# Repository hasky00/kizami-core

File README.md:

# kizami-core

The FPGA side of [Kizami](https://github.com/hasky00/kizami) — a Nostr-timestamped
audio witness. Runs on the open-hardware Alhambra II (iCE40HX4K).

- `rtl/` — Verilog. `timecode.v` is the HH:MM:SS:FF counter, `top.v` maps it to LEDs.
- `icestudio/` — `.ice` designs for Icestudio / FPGALab.
- `labs/` — FPGALab workbench configs.
- `docs/` — LTC frame layout and the roadmap.

## Simulate (no hardware)
1. Open `icestudio/` design in Icestudio, build once so `ice-build/` exists.
2. `fpga-lab --ice icestudio/<design>.ice --clock-hz 1200000` (slow mode, readable LEDs).

## Build & flash (Alhambra II)
```
pip install apio && apio install --all
apio build && apio upload
```

LED0–4 = frame count in binary, LED7 = blinks once per second.

License: MIT

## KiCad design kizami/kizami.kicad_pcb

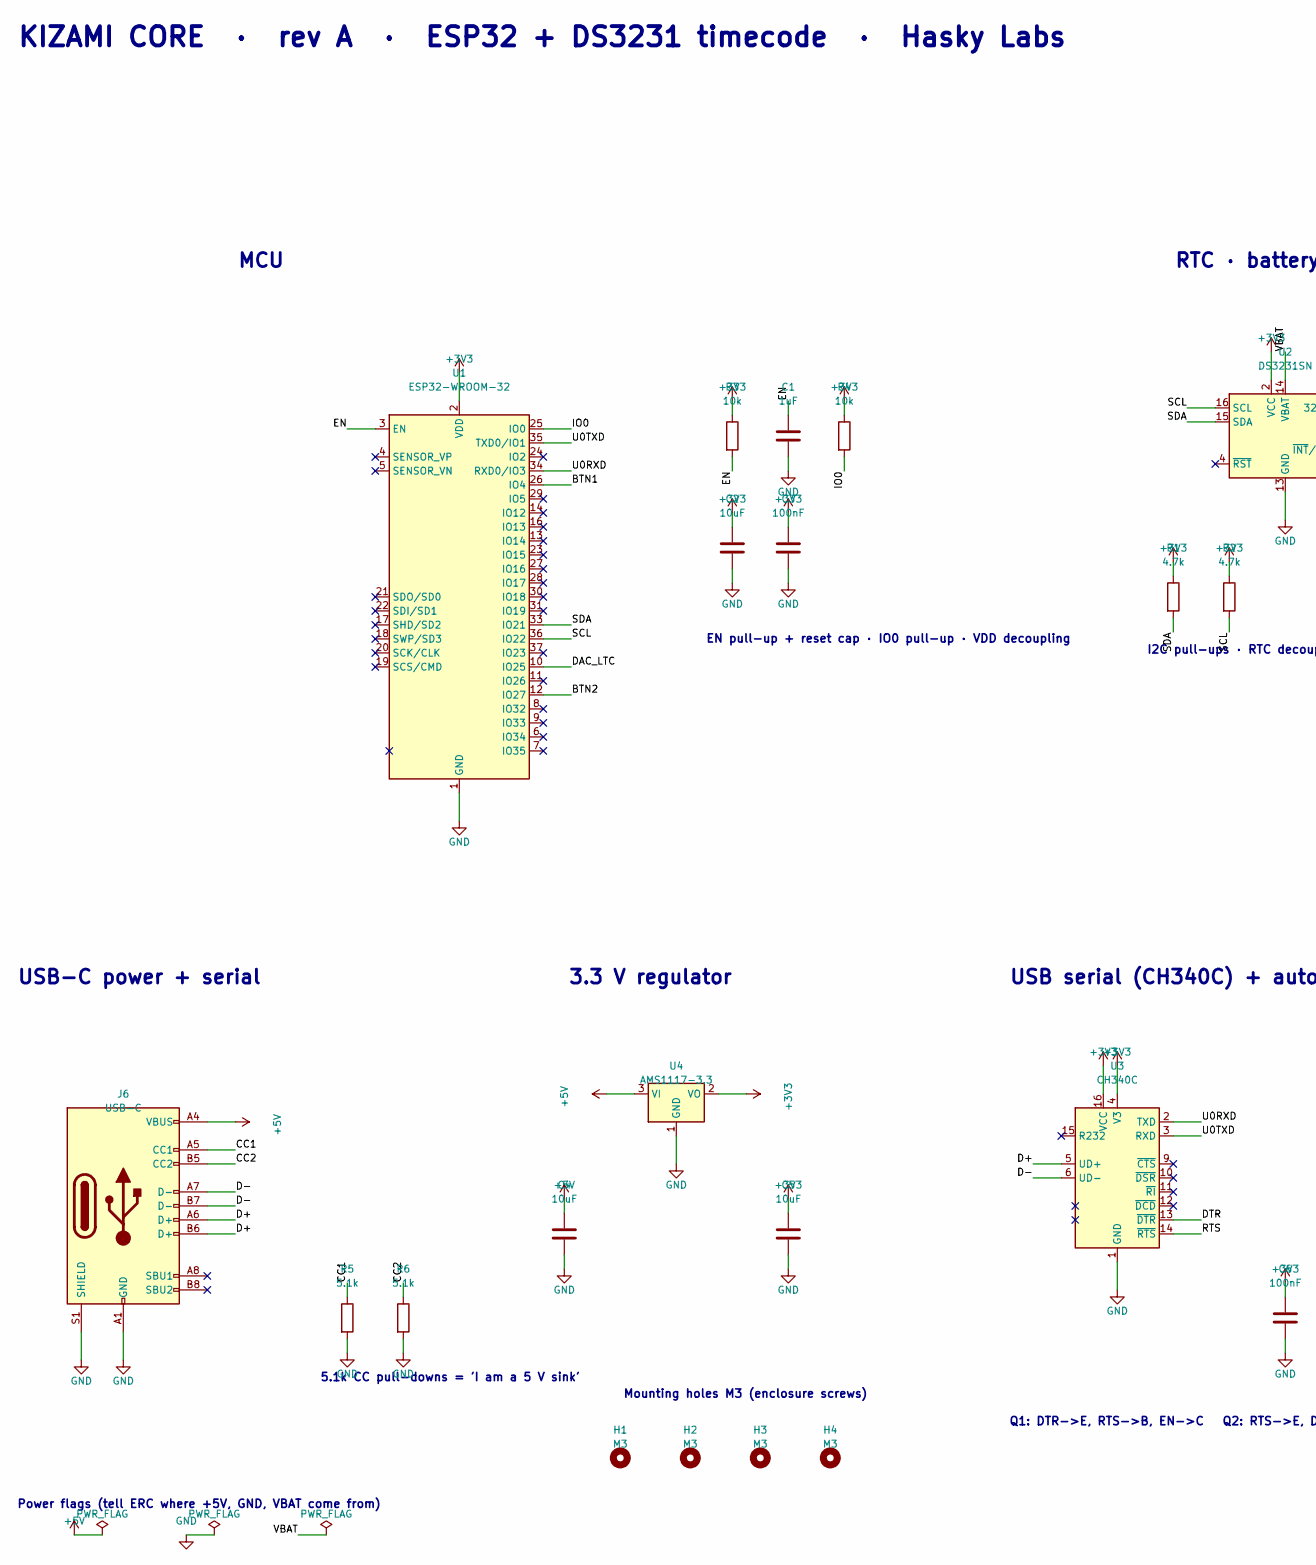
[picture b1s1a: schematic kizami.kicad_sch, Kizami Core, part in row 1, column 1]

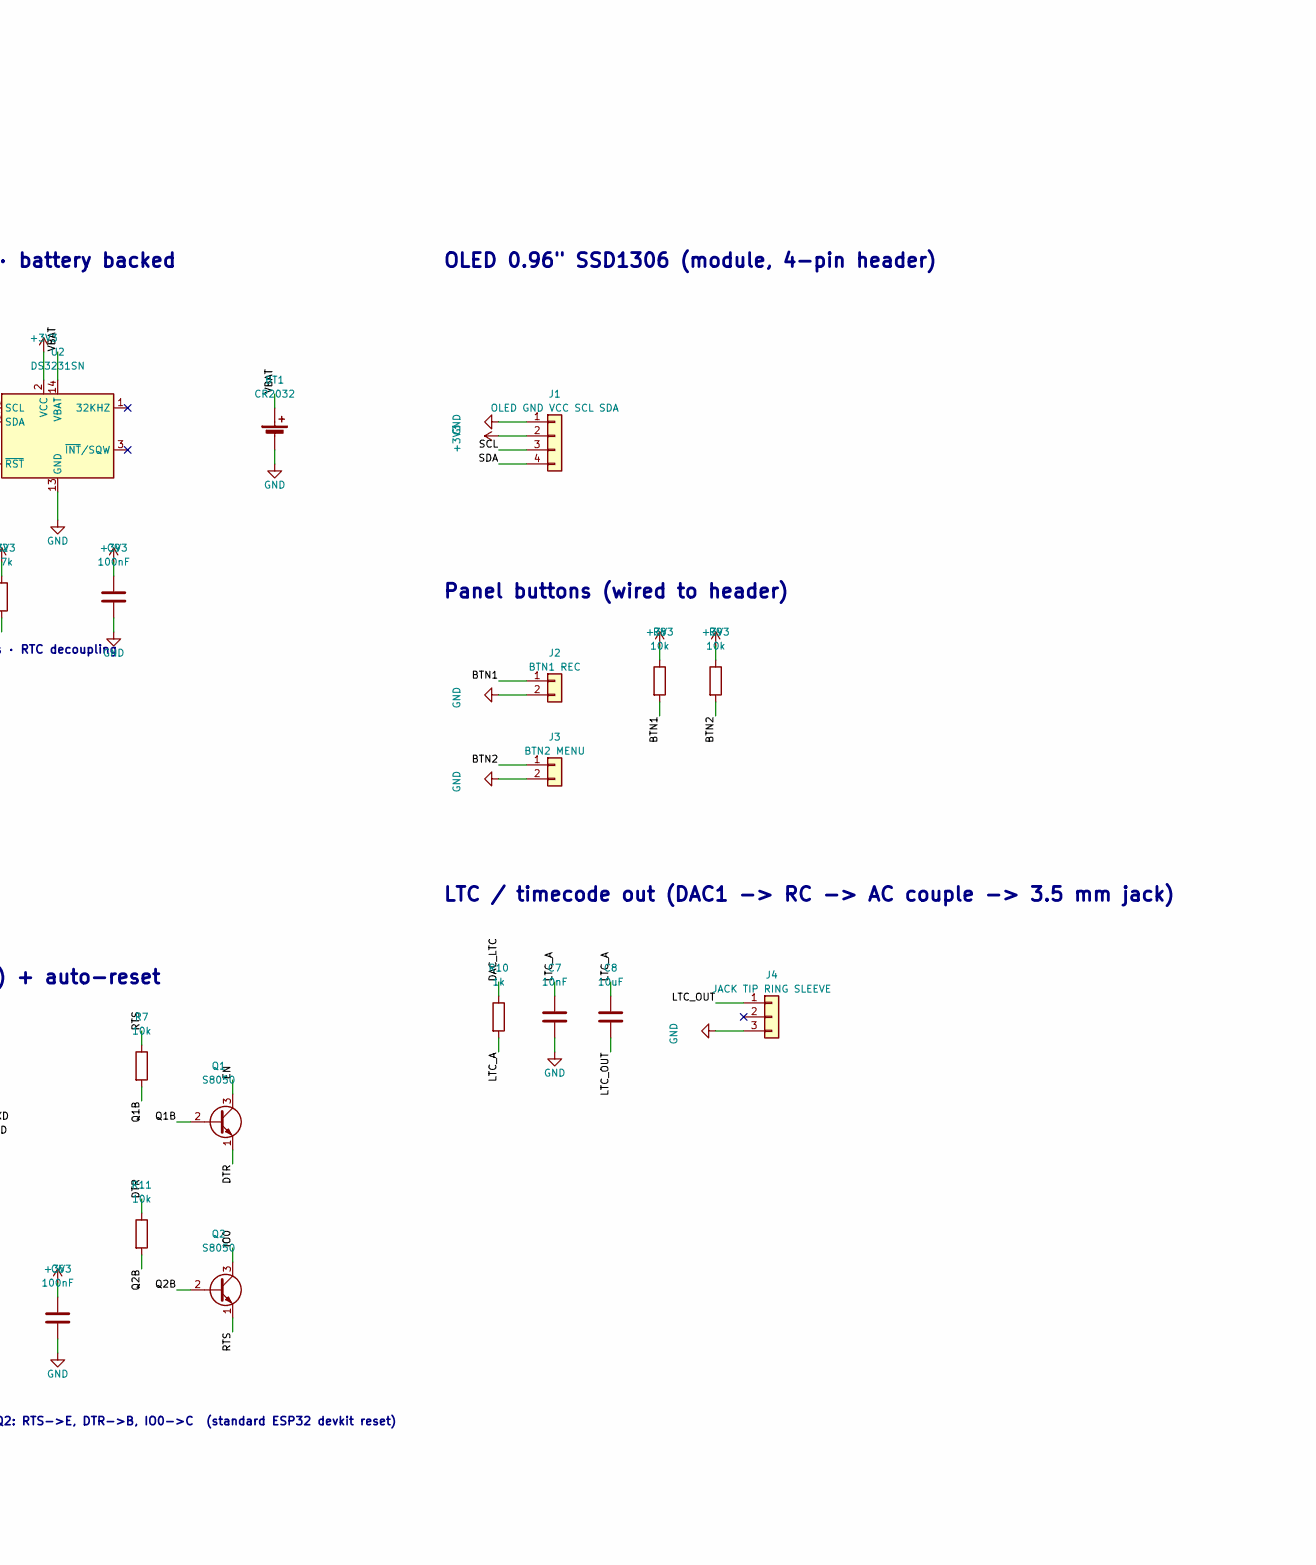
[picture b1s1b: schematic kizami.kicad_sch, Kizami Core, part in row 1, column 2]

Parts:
BT1: CR2032; BatteryHolder_Keystone_3034_1x20mm
C1: 1uF; C_0603_1608Metric; LCSC C15849
C2, C4, C5, C8: 10uF; C_0603_1608Metric; LCSC C19702
C3, C6, C9: 100nF; C_0603_1608Metric; LCSC C14663
C7: 10nF; C_0603_1608Metric; LCSC C57112
H1, H2, H3, H4: M3; MountingHole_3.2mm_M3
J1: OLED GND VCC SCL SDA; PinHeader_1x04_P2.54mm_Vertical
J2: BTN1 REC; PinHeader_1x02_P2.54mm_Vertical
J3: BTN2 MENU; PinHeader_1x02_P2.54mm_Vertical
J4: JACK TIP RING SLEEVE; PinHeader_1x03_P2.54mm_Vertical
J6: USB-C; USB_C_Receptacle_HRO_TYPE-C-31-M-12; LCSC C165948
Q1, Q2: S8050; SOT-23; LCSC C2146
R1, R2: 4.7k; R_0603_1608Metric; LCSC C23162
R3, R4, R7, R8, R9, R11: 10k; R_0603_1608Metric; LCSC C25804
R5, R6: 5.1k; R_0603_1608Metric; LCSC C23186
R10: 1k; R_0603_1608Metric; LCSC C21190
U1: ESP32-WROOM-32; LCSC C82899
U2: DS3231SN; SOIC-16W_7.5x10.3mm_P1.27mm
U3: CH340C; SOIC-16_3.9x9.9mm_P1.27mm; LCSC C84681
U4: AMS1117-3.3; SOT-223-3_TabPin2; LCSC C6186

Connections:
+3V3: C2.1, C3.1, C5.1, C6.1, C9.1, J1.2, R1.1, R2.1, R3.1, R4.1, R8.1, R9.1, U1.2 (VDD), U2.2 (VCC), U3.4 (V3), U3.16 (VCC), U4.2 (VO)
+5V: C4.1, J6.A4 (VBUS), J6.A9 (VBUS), J6.B4 (VBUS), J6.B9 (VBUS), U4.3 (VI)
/BTN1: J2.1, R8.2, U1.26 (IO4)
/BTN2: J3.1, R9.2, U1.12 (IO27)
/CC1: J6.A5 (CC1), R5.1
/CC2: J6.B5 (CC2), R6.1
/D+: J6.A6 (D+), J6.B6 (D+), U3.5 (UD+)
/D-: J6.A7 (D-), J6.B7 (D-), U3.6 (UD-)
/DAC_LTC: R10.1, U1.10 (IO25)
/DTR: Q1.1 (E), R11.1, U3.13 (~DTR)
/EN: C1.1, Q1.3 (C), R3.2, U1.3 (EN)
/IO0: Q2.3 (C), R4.2, U1.25 (IO0)
/LTC_A: C7.1, C8.1, R10.2
/LTC_OUT: C8.2, J4.1
/Q1B: Q1.2 (B), R7.2
/Q2B: Q2.2 (B), R11.2
/RTS: Q2.1 (E), R7.1, U3.14 (~RTS)
/SCL: J1.3, R2.2, U1.36 (IO22), U2.16 (SCL)
/SDA: J1.4, R1.2, U1.33 (IO21), U2.15 (SDA)
/U0RXD: U1.34 (RXD0/IO3), U3.2 (TXD)
/U0TXD: U1.35 (TXD0/IO1), U3.3 (RXD)
/VBAT: BT1.1 (+), U2.14 (VBAT)
GND: BT1.2 (-), C1.2, C2.2, C3.2, C4.2, C5.2, C6.2, C7.2, C9.2, J1.1, J2.2, J3.2, J4.3, J6.A1 (GND), J6.A12 (GND), J6.B1 (GND), J6.B12 (GND), J6.S1 (SHIELD), R5.2, R6.2, U1.1 (GND), U1.15 (GND), U1.38 (GND), U1.39 (GND), U2.5 (GND), U2.6 (GND), U2.7 (GND), U2.8 (GND), U2.9 (GND), U2.10 (GND), U2.11 (GND), U2.12 (GND), U2.13 (GND), U3.1 (GND), U4.1 (GND)

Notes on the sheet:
KIZAMI CORE · rev A · ESP32 + DS3231 timecode · Hasky Labs
MCU
EN pull-up + reset cap · IO0 pull-up · VDD decoupling
RTC · battery backed
I2C pull-ups · RTC decoupling
OLED 0.96" SSD1306 (module, 4-pin header)
Panel buttons (wired to header)
LTC / timecode out (DAC1 -> RC -> AC couple -> 3.5 mm jack)
USB-C power + serial
5.1k CC pull-downs = 'I am a 5 V sink'
3.3 V regulator
USB serial (CH340C) + auto-reset
Q1: DTR->E, RTS->B, EN->C Q2: RTS->E, DTR->B, IO0->C (standard ESP32 devkit reset)
Power flags (tell ERC where +5V, GND, VBAT come from)
Mounting holes M3 (enclosure screws)

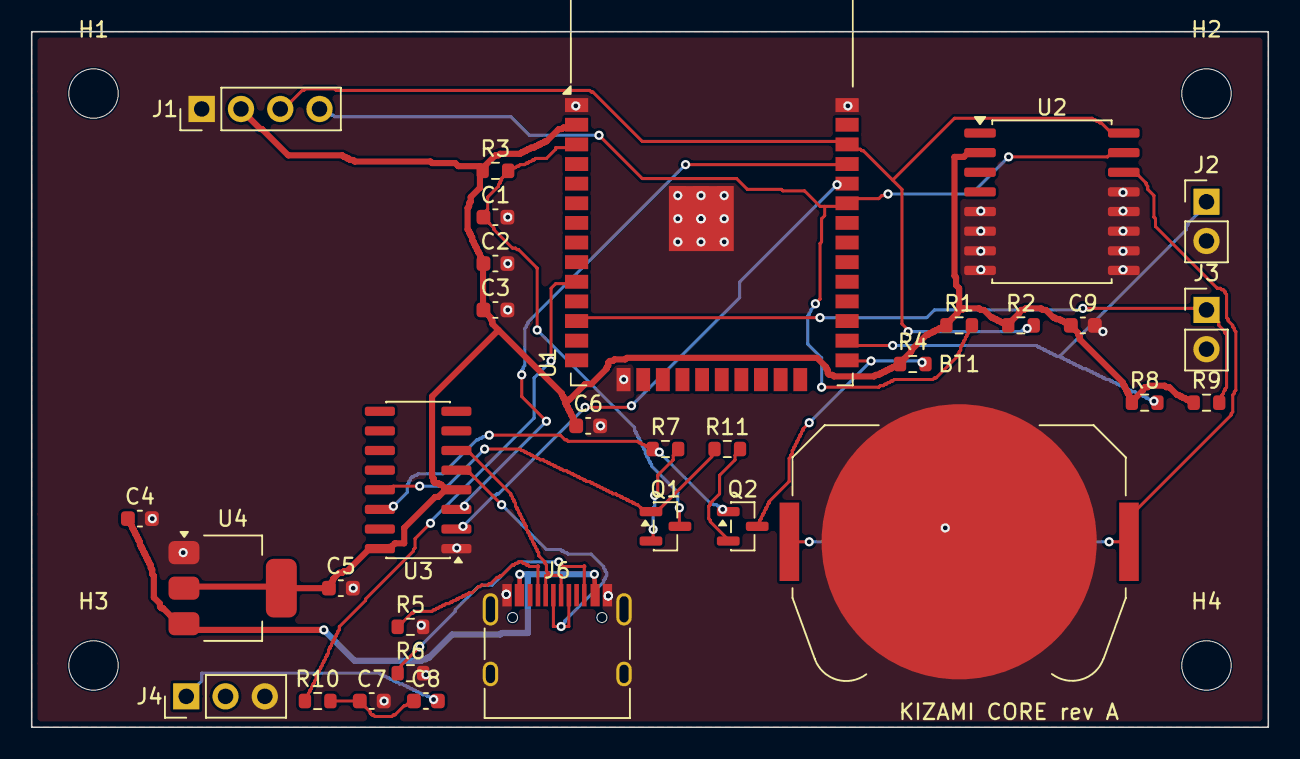
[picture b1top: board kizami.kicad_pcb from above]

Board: 2 copper layers, 80.0 x 45.0 mm, 36 parts (0 on the bottom side), 23 nets.
